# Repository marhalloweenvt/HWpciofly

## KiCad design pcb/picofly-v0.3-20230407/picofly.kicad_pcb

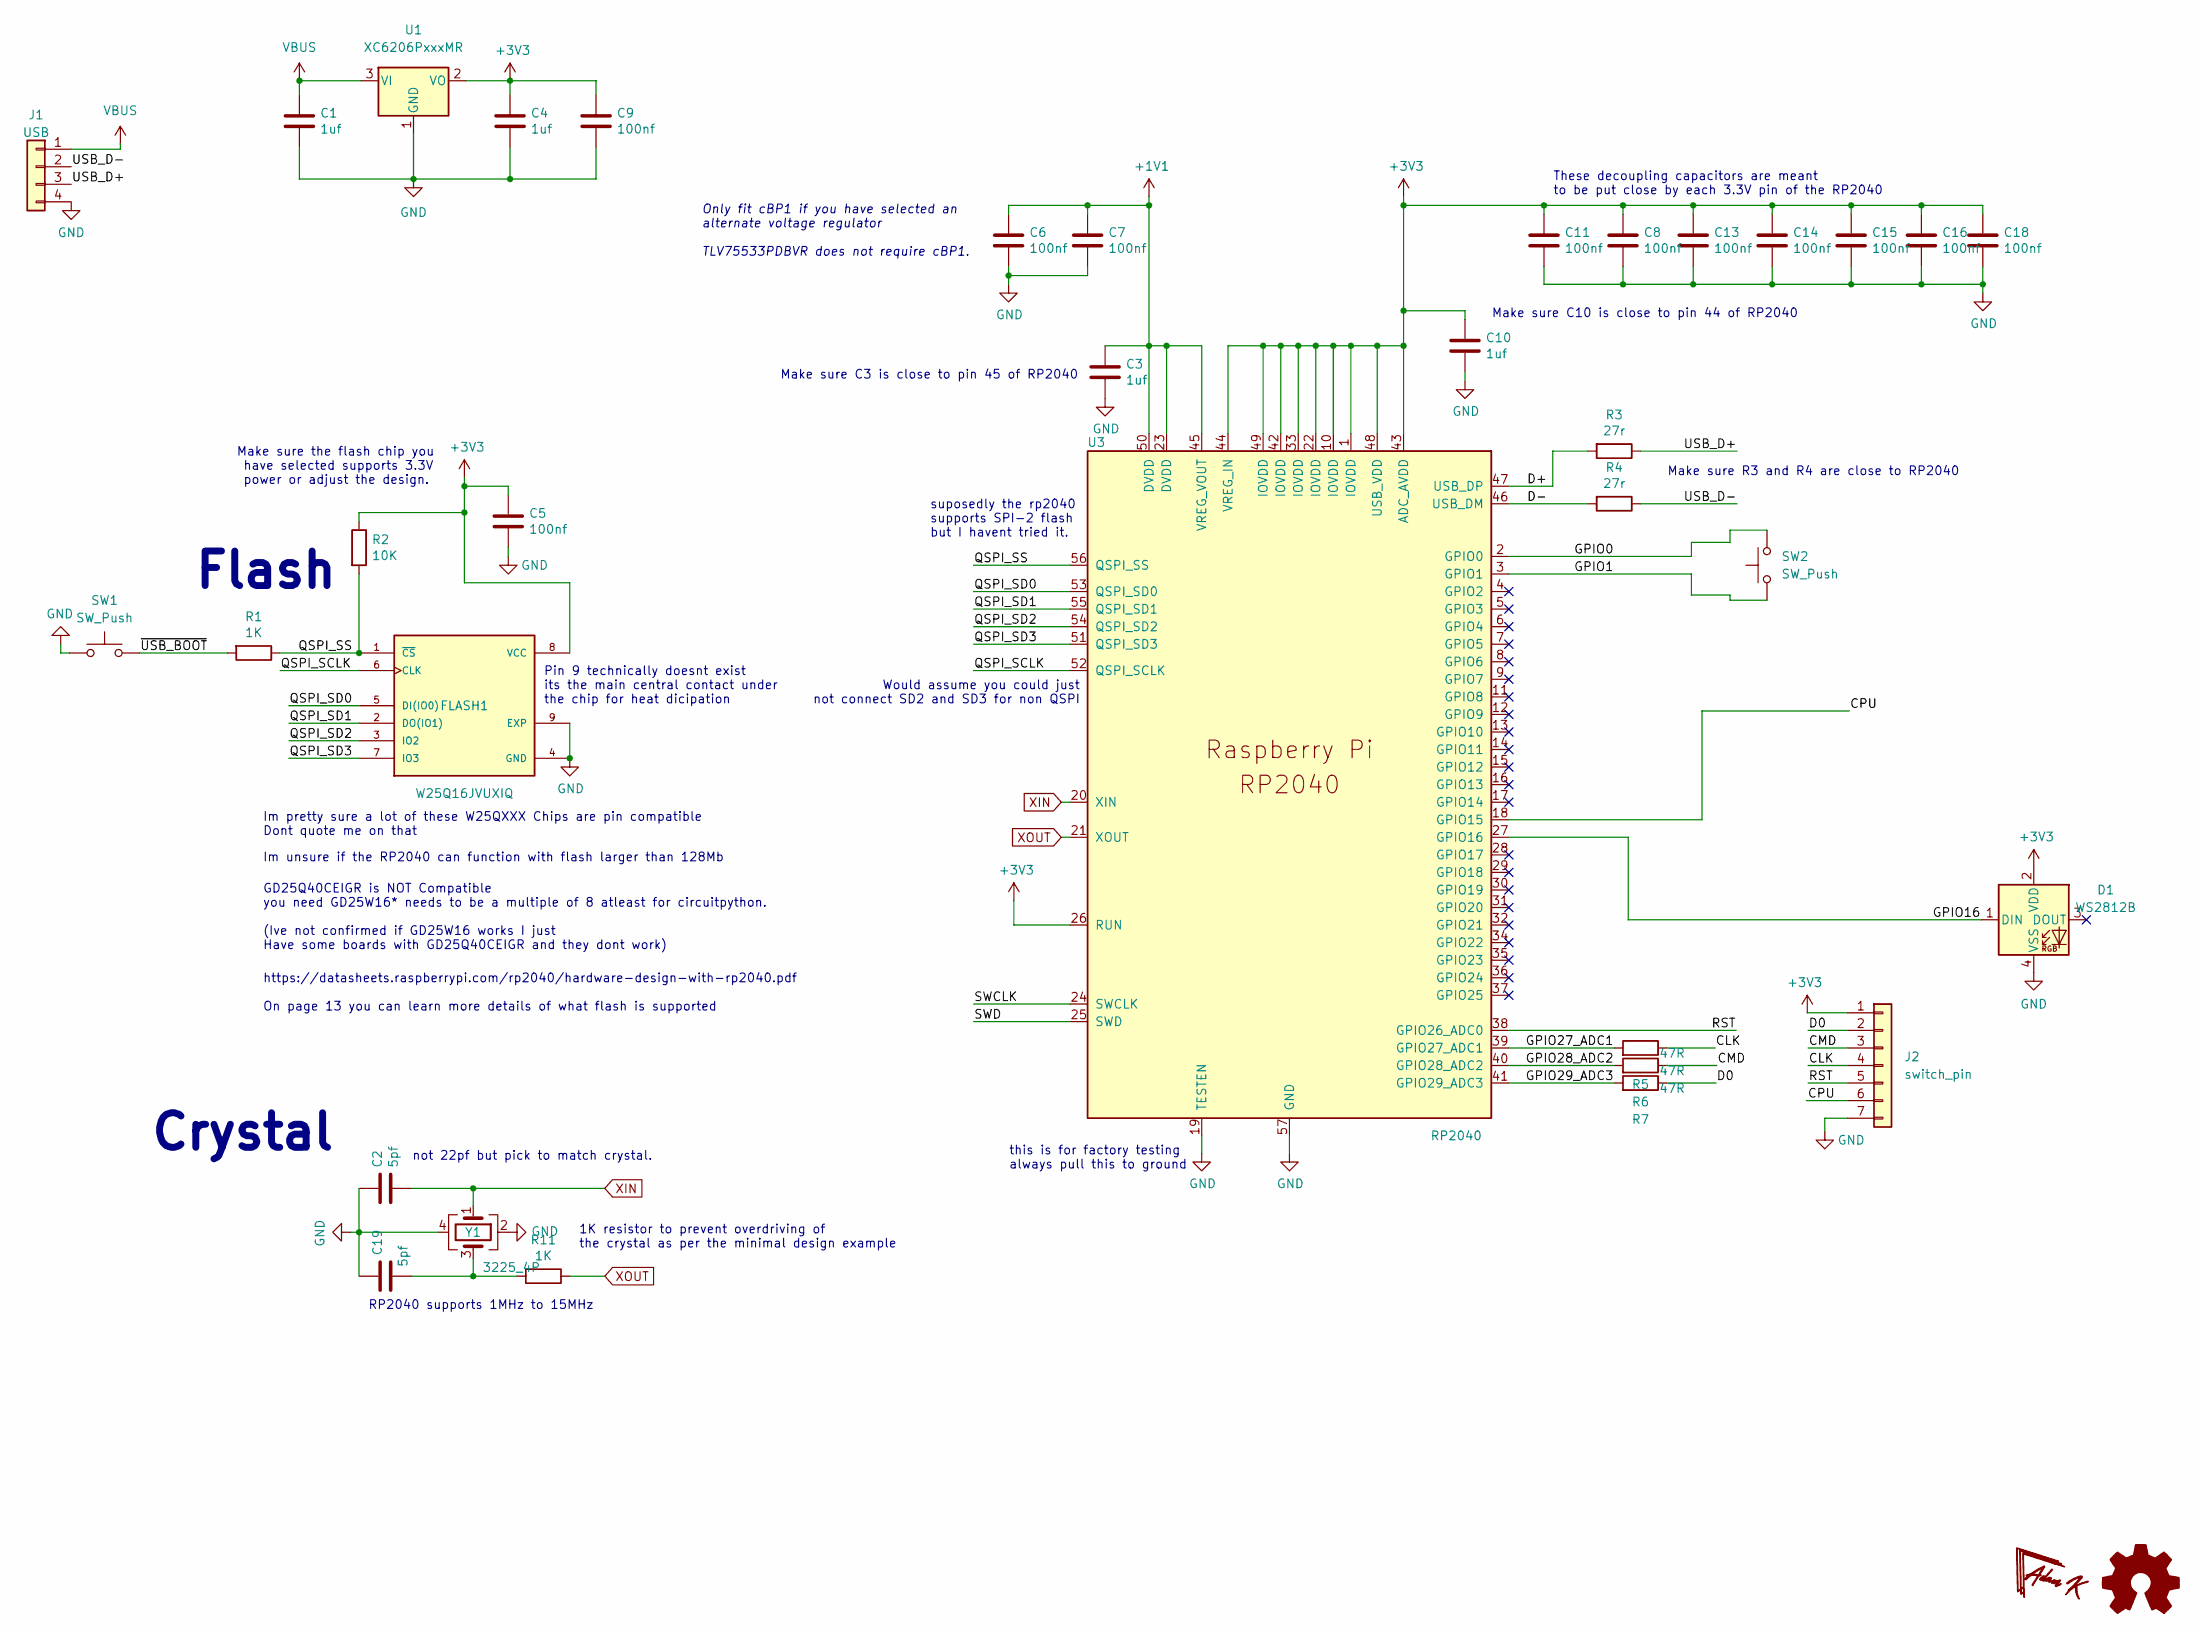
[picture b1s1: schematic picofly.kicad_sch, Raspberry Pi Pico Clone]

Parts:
C1, C3, C4, C10: 1uf; C_0402_1005Metric
C2, C19: 5pf; C_0402_1005Metric
C5, C6, C7, C8, C9, C11, C13, C14, C15, C16, C18: 100nf; C_0402_1005Metric
D1: WS2812B; LED_WS2812-2020
FLASH1: W25Q16JVUXIQ; USON-8_2x3mm_P0.5mm
J1: USB; pico_usb_point
J2: switch_pin; PICO_TESTPoint
R1, R11: 1K; R_0402_1005Metric
R2: 10K; R_0402_1005Metric
R3, R4: 27r; R_0402_1005Metric
R5, R6, R7: 47R; R_0402_1005Metric
SW1, SW2: SW_Push; SW-K2-1828UQ
U1: XC6206PxxxMR; SOT-23
U3: RP2040; RP2040-QFN-56; LCSC C2040
Y1: 3225_4P; Crystal_SMD_3225-4Pin_3.2x2.5mm

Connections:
+1V1: C3.1, C6.1, C7.1, U3.23 (DVDD), U3.45 (VREG_VOUT), U3.50 (DVDD)
+3V3: C4.1, C5.1, C8.1, C9.1, C10.1, C11.1, C13.1, C14.1, C15.1, C16.1, C18.1, D1.2 (VDD), FLASH1.8 (VCC), J2.1, R2.1, U1.2 (VO), U3.1 (IOVDD), U3.10 (IOVDD), U3.22 (IOVDD), U3.26 (RUN), U3.33 (IOVDD), U3.42 (IOVDD), U3.43 (ADC_AVDD), U3.44 (VREG_IN), U3.48 (USB_VDD), U3.49 (IOVDD)
/CLK: J2.4, R5.1
/CMD: J2.3, R6.1
/CPU: J2.6, U3.18 (GPIO15)
/D0: J2.2, R7.1
/D+: R3.2, U3.47 (USB_DP)
/D-: R4.2, U3.46 (USB_DM)
/GPIO0: SW2.2, U3.2 (GPIO0)
/GPIO1: SW2.1, U3.3 (GPIO1)
/GPIO16: D1.1 (DIN), U3.27 (GPIO16)
/GPIO27_ADC1: R5.2, U3.39 (GPIO27_ADC1)
/GPIO28_ADC2: R6.2, U3.40 (GPIO28_ADC2)
/GPIO29_ADC3: R7.2, U3.41 (GPIO29_ADC3)
/QSPI_SCLK: FLASH1.6 (CLK), U3.52 (QSPI_SCLK)
/QSPI_SD0: FLASH1.5 (DI(IO0)), U3.53 (QSPI_SD0)
/QSPI_SD1: FLASH1.2 (DO(IO1)), U3.55 (QSPI_SD1)
/QSPI_SD2: FLASH1.3 (IO2), U3.54 (QSPI_SD2)
/QSPI_SD3: FLASH1.7 (IO3), U3.51 (QSPI_SD3)
/QSPI_SS: FLASH1.1 (~CS), R1.1, R2.2, U3.56 (QSPI_SS)
/RST: J2.5, U3.38 (GPIO26_ADC0)
/SWCLK: U3.24 (SWCLK)
/SWD: U3.25 (SWD)
/USB_D+: J1.3, R3.1
/USB_D-: J1.2, R4.1
/~USB_BOOT: R1.2, SW1.2
GND: C1.2, C2.1, C3.2, C4.2, C5.2, C6.2, C7.2, C8.2, C9.2, C10.2, C11.2, C13.2, C14.2, C15.2, C16.2, C18.2, C19.1, D1.4 (VSS), FLASH1.4 (GND), FLASH1.9 (EXP), J1.4, J2.7, SW1.1, U1.1 (GND), U3.19 (TESTEN), U3.57 (GND), Y1.2, Y1.4
unnamed: C19.2, R11.2, Y1.3
VBUS: C1.1, J1.1, U1.3 (VI)
XIN: C2.2, U3.20 (XIN), Y1.1
XOUT: R11.1, U3.21 (XOUT)

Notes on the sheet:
GD25Q40CEIGR is NOT Compatible you need GD25W16* needs to be a multiple of 8 atleast for circuitpython. (Ive not confirmed if GD25W16 works I just Have some boards with GD25Q40CEIGR and they dont work)
https://datasheets.raspberrypi.com/rp2040/hardware-design-with-rp2040.pdf On page 13 you can learn more details of what flash is supported
Only fit cBP1 if you have selected an alternate voltage regulator TLV75533PDBVR does not require cBP1.
Pin 9 technically doesnt exist its the main central contact under the chip for heat dicipation
Make sure R3 and R4 are close to RP2040
this is for factory testing always pull this to ground
Im unsure if the RP2040 can function with flash larger than 128Mb
Would assume you could just not connect SD2 and SD3 for non QSPI
These decoupling capacitors are meant to be put close by each 3.3V pin of the RP2040
Flash
Im pretty sure a lot of these W25QXXX Chips are pin compatible Dont quote me on that
not 22pf but pick to match crystal.
suposedly the rp2040 supports SPI-2 flash but I havent tried it.
1K resistor to prevent overdriving of the crystal as per the minimal design example
RP2040 supports 1MHz to 15MHz
Make sure the flash chip you have selected supports 3.3V power or adjust the design.
Crystal
Make sure C3 is close to pin 45 of RP2040
Make sure C10 is close to pin 44 of RP2040

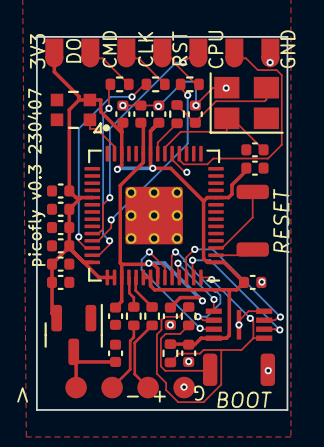
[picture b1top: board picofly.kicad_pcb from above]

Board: 2 copper layers, 13.9 x 20.7 mm, 34 parts (0 on the bottom side), 29 nets.
